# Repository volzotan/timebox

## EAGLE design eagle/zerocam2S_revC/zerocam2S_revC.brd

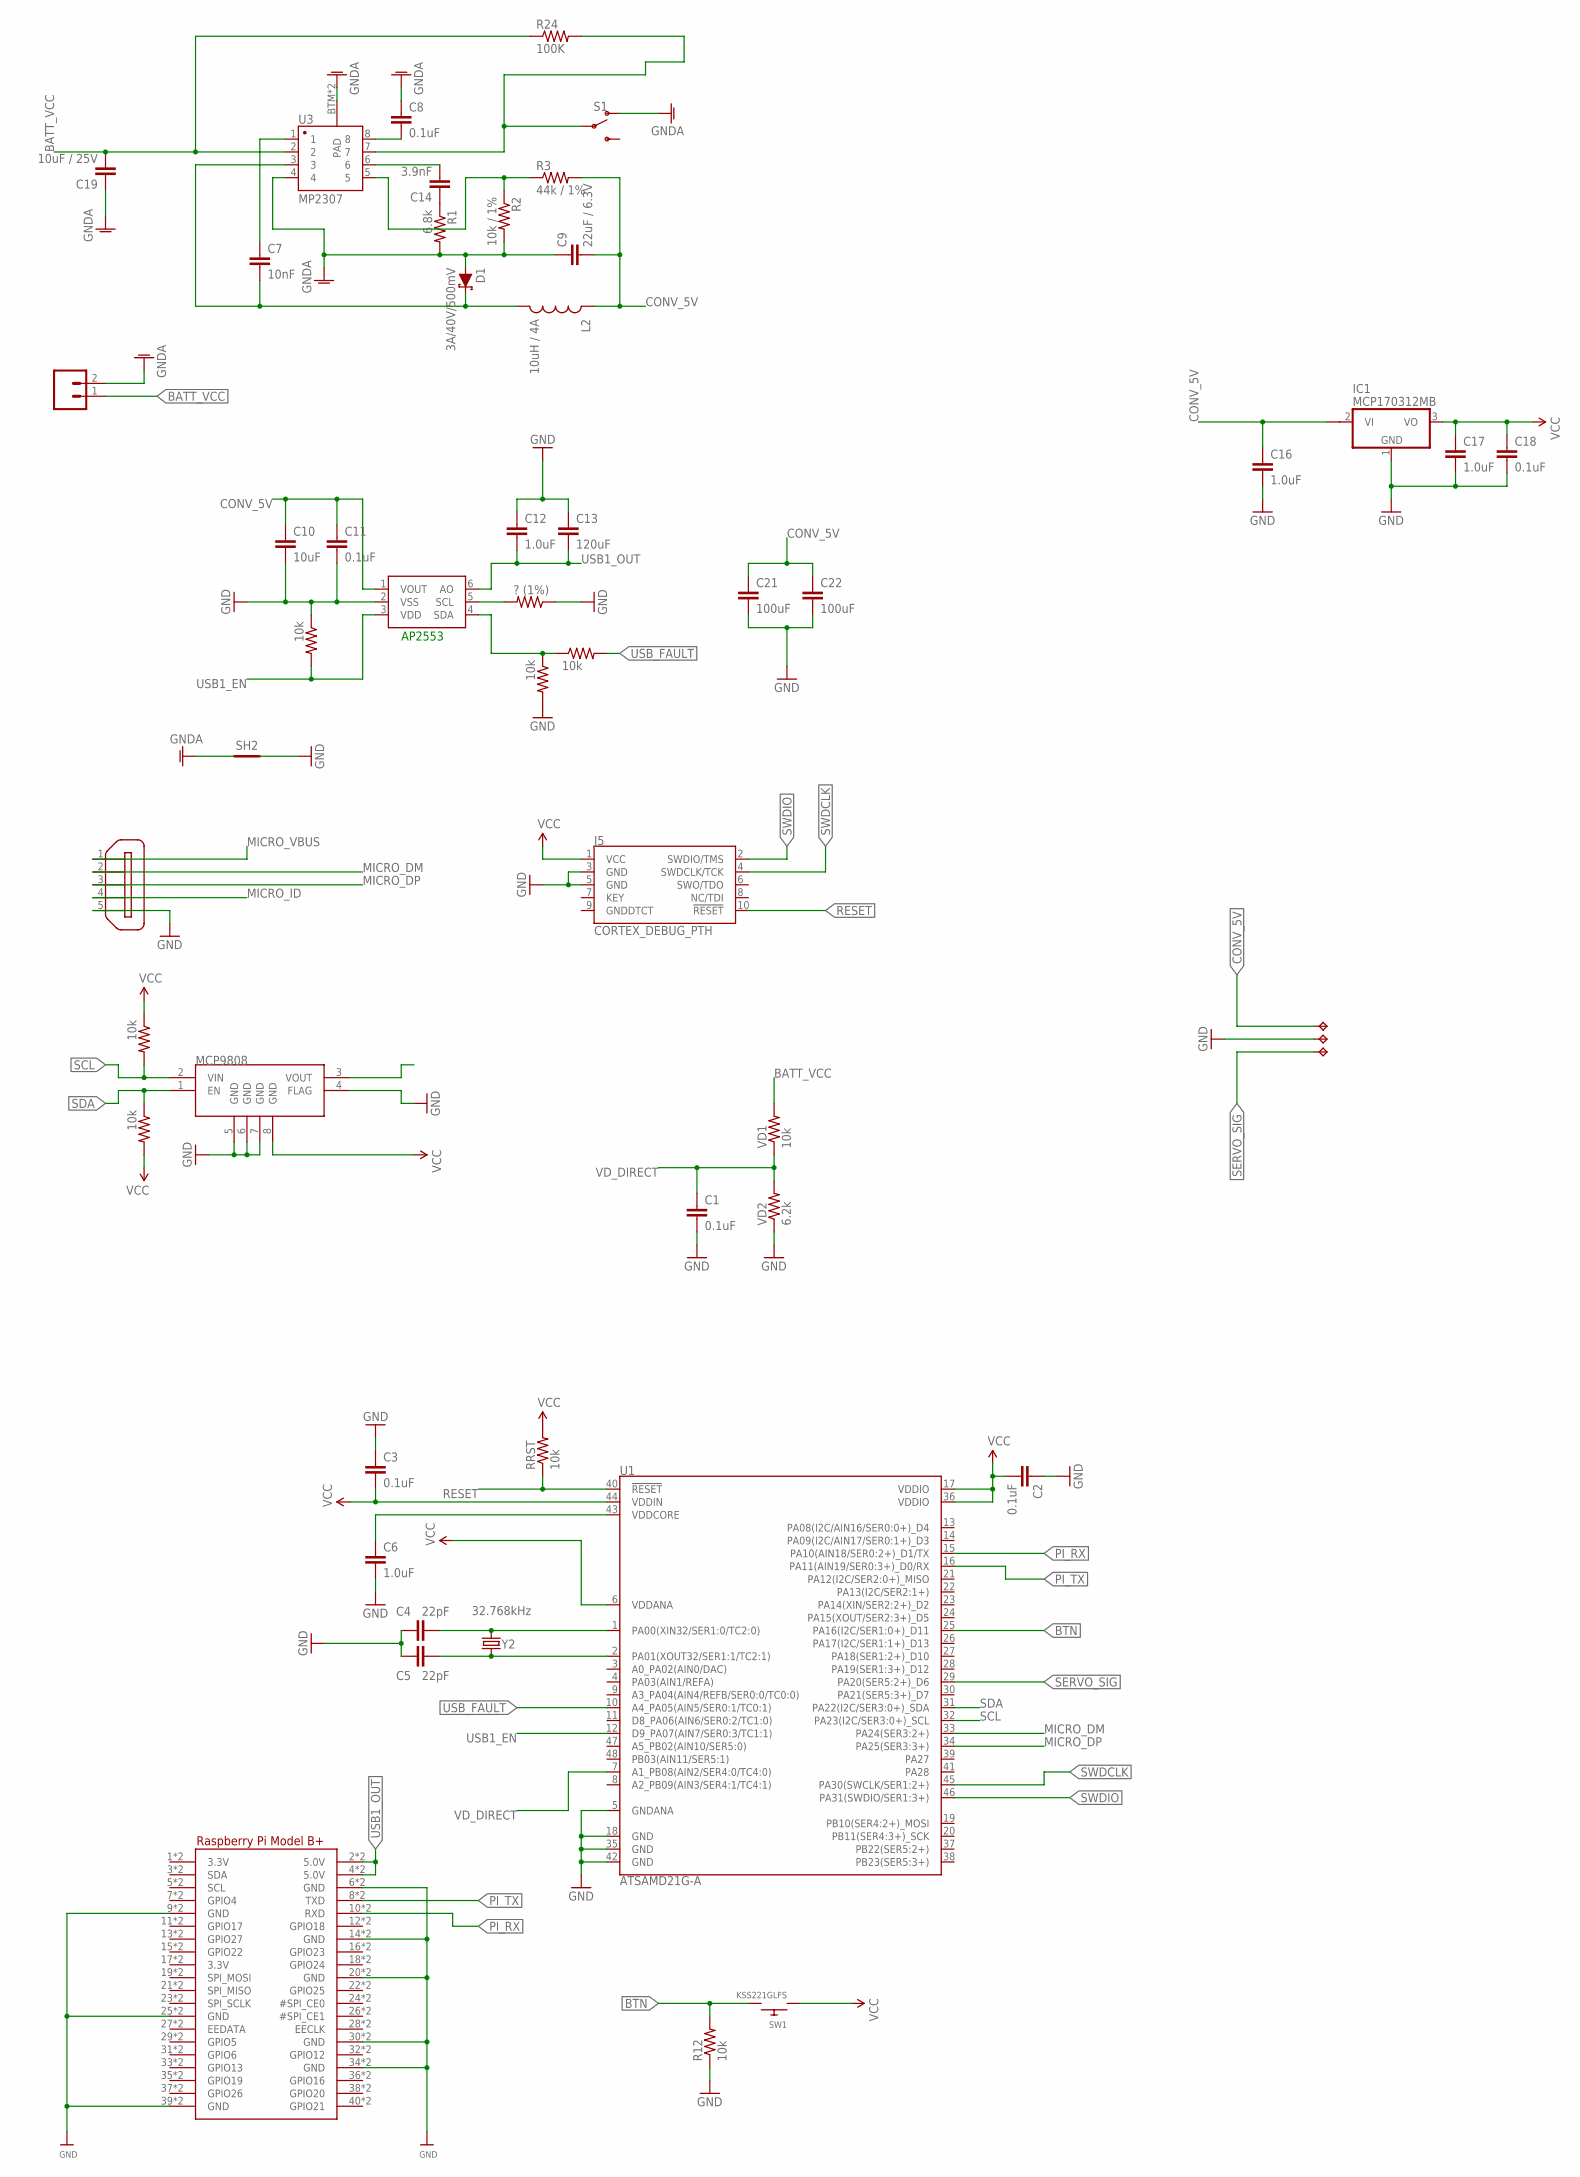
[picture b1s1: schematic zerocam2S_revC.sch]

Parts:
AP2553: MCP4725; SOT23-6
C1, C2, C3, C11, C18: 0.1uF; 0805
C4, C5: 22pF; 0805
C6, C16: 1.0uF; 0805
C7: 10nF; 0805
C8: 0.1uF; 1206
C9: 22uF / 6.3V; 1210
C10: 10uF; 0805
C12, C17: 1.0uF; 1206
C13: 120uF; 1206
C14: 3.9nF; 1206
C19: 10uF / 25V; 1210
C21, C22: 100uF; 1210
D1: 3A/40V/500mV; SMA-DIODE
IC1: MCP170312MB; SOT89
J1: CONN_023.5MM-NO_SILK; SCREWTERMINAL-3.5MM-2-NS
J5: CORTEX_DEBUG_PTH; 2X5-PTH-1.27MM
L2: 10uH / 4A; SRU1038
MCP9808: V_REG_MIC5216; MSOP8
R1: 6.8k; 1206
R2: 10k / 1%; 1206
R3: 44k / 1%; 1206
R12: 10k; 0805
R24: 100K; 1206
RPI1: RASPBERRYPI_BPLUS_BONNET_THMSMT; PI_BONNET_THMSMT
RRST: 10k; 0805
R_I2C_1, R_I2C_2: 10k; 0805
R_MOSFET_USB1: ? (1%); 0805
R_MOSFET_USB2, R_MOSFET_USB3, R_MOSFET_USB4: 10k; 0805
S1: SWITCH-SPDT-SMD-RIGHT-ANGLE; SWITCH_SPST_SMD_A
SH2: SHORT-HT5; SHORT_TOP-50
SW1: KSS221GLFS; BTN_CK_KSS
TP1, TP2, TP3: TPTP20SQ; TP20SQ
U1: ATSAMD21G-A; TQFP-48
U3: MP2307; SO08
VD1: 10k; 0805
VD2: 6.2k; 0805
X2: ZX62D-B-5PA8
Y2: 32.768kHz; CRYSTAL-SMD-3.2X1.5MM

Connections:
BATT_VCC: C19.2, J1.1, R24.1, U3.2, VD1.2
BTN: R12.2, SW1.P$2, U1.25 (PA16(I2C/SER1:0+)_D11)
CONV_5V: AP2553.1 (VOUT), C9.2, C10.1, C11.1, C16.1, C21.1, C22.1, IC1.2@1 (VI1), L2.1, R3.2, TP1.TP
GND: AP2553.2 (VSS), C1.2, C2.1, C3.1, C4.1, C5.1, C6.2, C10.2, C11.2, C12.1, C13.1, C16.2, C17.2, C18.2, C21.2, C22.2, IC1.1 (GND), J5.3 (GND), J5.5 (GND), MCP9808.4 (FLAG), MCP9808.5 (GND), MCP9808.6 (GND), MCP9808.7 (GND), R12.1, RPI1.6 (GND), RPI1.9 (GND), RPI1.14 (GND), RPI1.20 (GND), RPI1.25 (GND), RPI1.30 (GND), RPI1.34 (GND), RPI1.39 (GND), RPI1.S6 (GND), RPI1.S9 (GND), RPI1.S14 (GND), RPI1.S20 (GND), RPI1.S25 (GND), RPI1.S30 (GND), RPI1.S34 (GND), RPI1.S39 (GND), R_MOSFET_USB1.1, R_MOSFET_USB2.2, R_MOSFET_USB3.1, SH2.2, TP2.TP, U1.5 (GNDANA), U1.18 (GND), U1.35 (GND), U1.42 (GND), VD2.1, X2.5
GNDA: C8.1, C9.1, C19.1, D1.A, J1.2, R1.2, R2.2, S1.1 (O), SH2.1, U3.4, U3.BTM (PAD), U3.P$1 (PAD)
MICRO_DM: U1.33 (PA24(SER3:2+)), X2.2
MICRO_DP: U1.34 (PA25(SER3:3+)), X2.3
MICRO_ID: X2.4
MICRO_VBUS: X2.1
unnamed: C6.1, U1.43 (VDDCORE)
unnamed: AP2553.5 (SCL), R_MOSFET_USB1.2
unnamed: AP2553.4 (SDA), R_MOSFET_USB2.1, R_MOSFET_USB4.1
unnamed: C4.2, U1.1 (PA00(XIN32/SER1:0/TC2:0)), Y2.P$2 (2)
unnamed: C8.2, U3.8
unnamed: C7.2, D1.C, L2.2, U3.3
unnamed: C7.1, U3.1
unnamed: C14.1, R1.1
unnamed: C14.2, U3.6
unnamed: R2.1, R3.1, U3.5
unnamed: C5.2, U1.2 (PA01(XOUT32/SER1:1/TC2:1)), Y2.P$1 (1)
PB_BUCK_EN: R24.2, S1.2, U3.7
PI_RX: RPI1.10 (RXD), RPI1.S10 (RXD), U1.15 (PA10(AIN18/SER0:2+)_D1/TX)
PI_TX: RPI1.8 (TXD), RPI1.S8 (TXD), U1.16 (PA11(AIN19/SER0:3+)_D0/RX)
RESET: J5.10 (!RESET), RRST.1, U1.40 (!RESET!)
SCL: MCP9808.2 (VIN), R_I2C_1.2, U1.32 (PA23(I2C/SER3:0+)_SCL)
SDA: MCP9808.1 (EN), R_I2C_2.1, U1.31 (PA22(I2C/SER3:0+)_SDA)
SERVO_SIG: TP3.TP, U1.29 (PA20(SER5:2+)_D6)
SWDCLK: J5.4 (SWDCLK/TCK), U1.45 (PA30(SWCLK/SER1:2+))
SWDIO: J5.2 (SWDIO/TMS), U1.46 (PA31(SWDIO/SER1:3+))
USB1_EN: AP2553.3 (VDD), R_MOSFET_USB3.2, U1.12 (D9_PA07(AIN7/SER0:3/TC1:1))
USB1_OUT: AP2553.6 (AO), C12.2, C13.2, RPI1.2 (5.0V), RPI1.4 (5.0V), RPI1.S2 (5.0V), RPI1.S4 (5.0V)
USB_FAULT: R_MOSFET_USB4.2, U1.10 (A4_PA05(AIN5/SER0:1/TC0:1))
VCC: C2.2, C3.2, C17.1, C18.1, IC1.3 (VO), J5.1 (VCC), MCP9808.8 (GND), RRST.2, R_I2C_1.1, R_I2C_2.2, SW1.P$1, U1.6 (VDDANA), U1.17 (VDDIO), U1.36 (VDDIO), U1.44 (VDDIN)
VD_DIRECT: C1.1, U1.7 (A1_PB08(AIN2/SER4:0/TC4:0)), VD1.1, VD2.2

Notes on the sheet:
AP2553

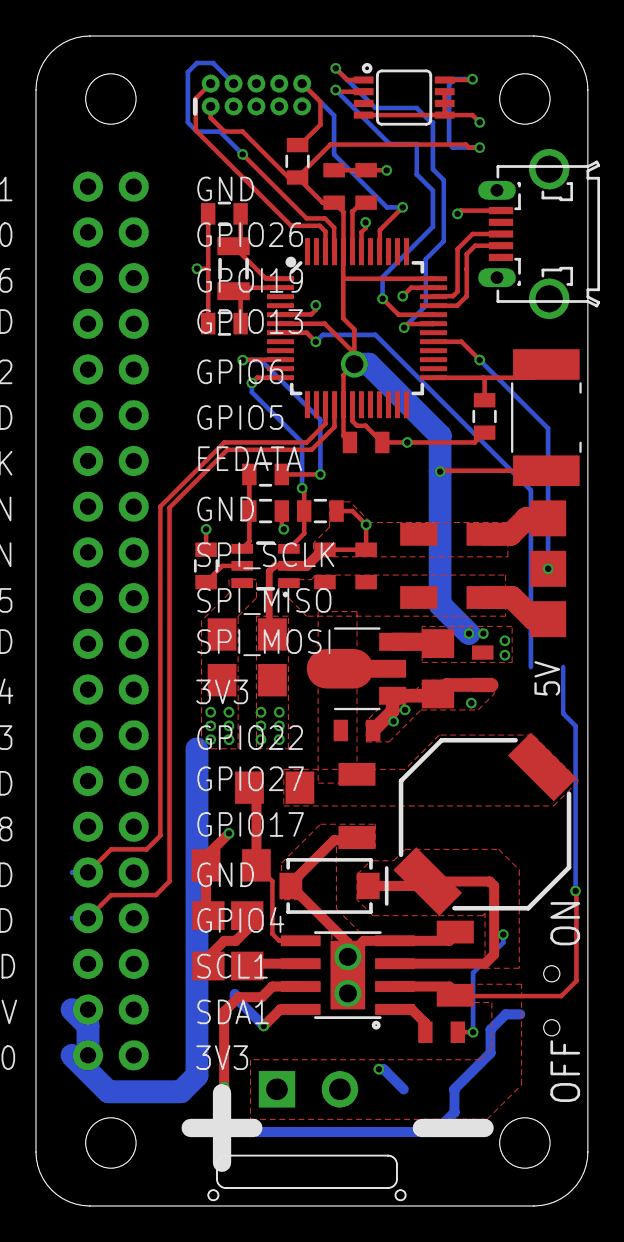
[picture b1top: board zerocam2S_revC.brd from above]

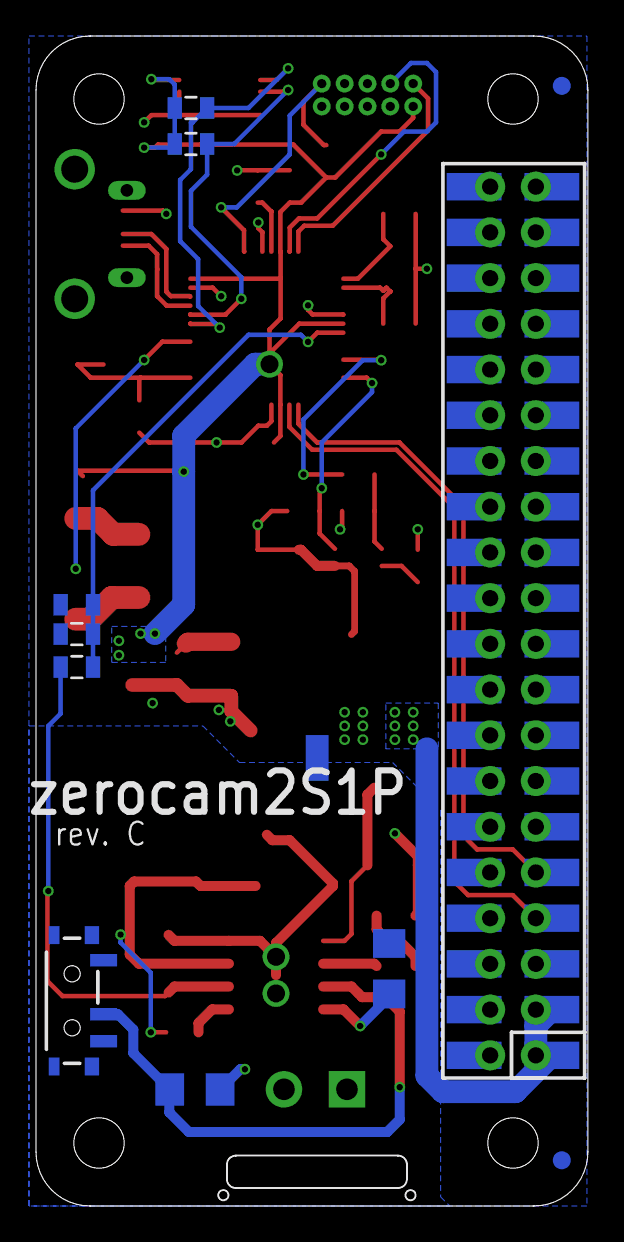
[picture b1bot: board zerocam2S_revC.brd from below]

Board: 2 copper layers, 30.7 x 65.0 mm, 52 parts (9 on the bottom side), 32 nets.

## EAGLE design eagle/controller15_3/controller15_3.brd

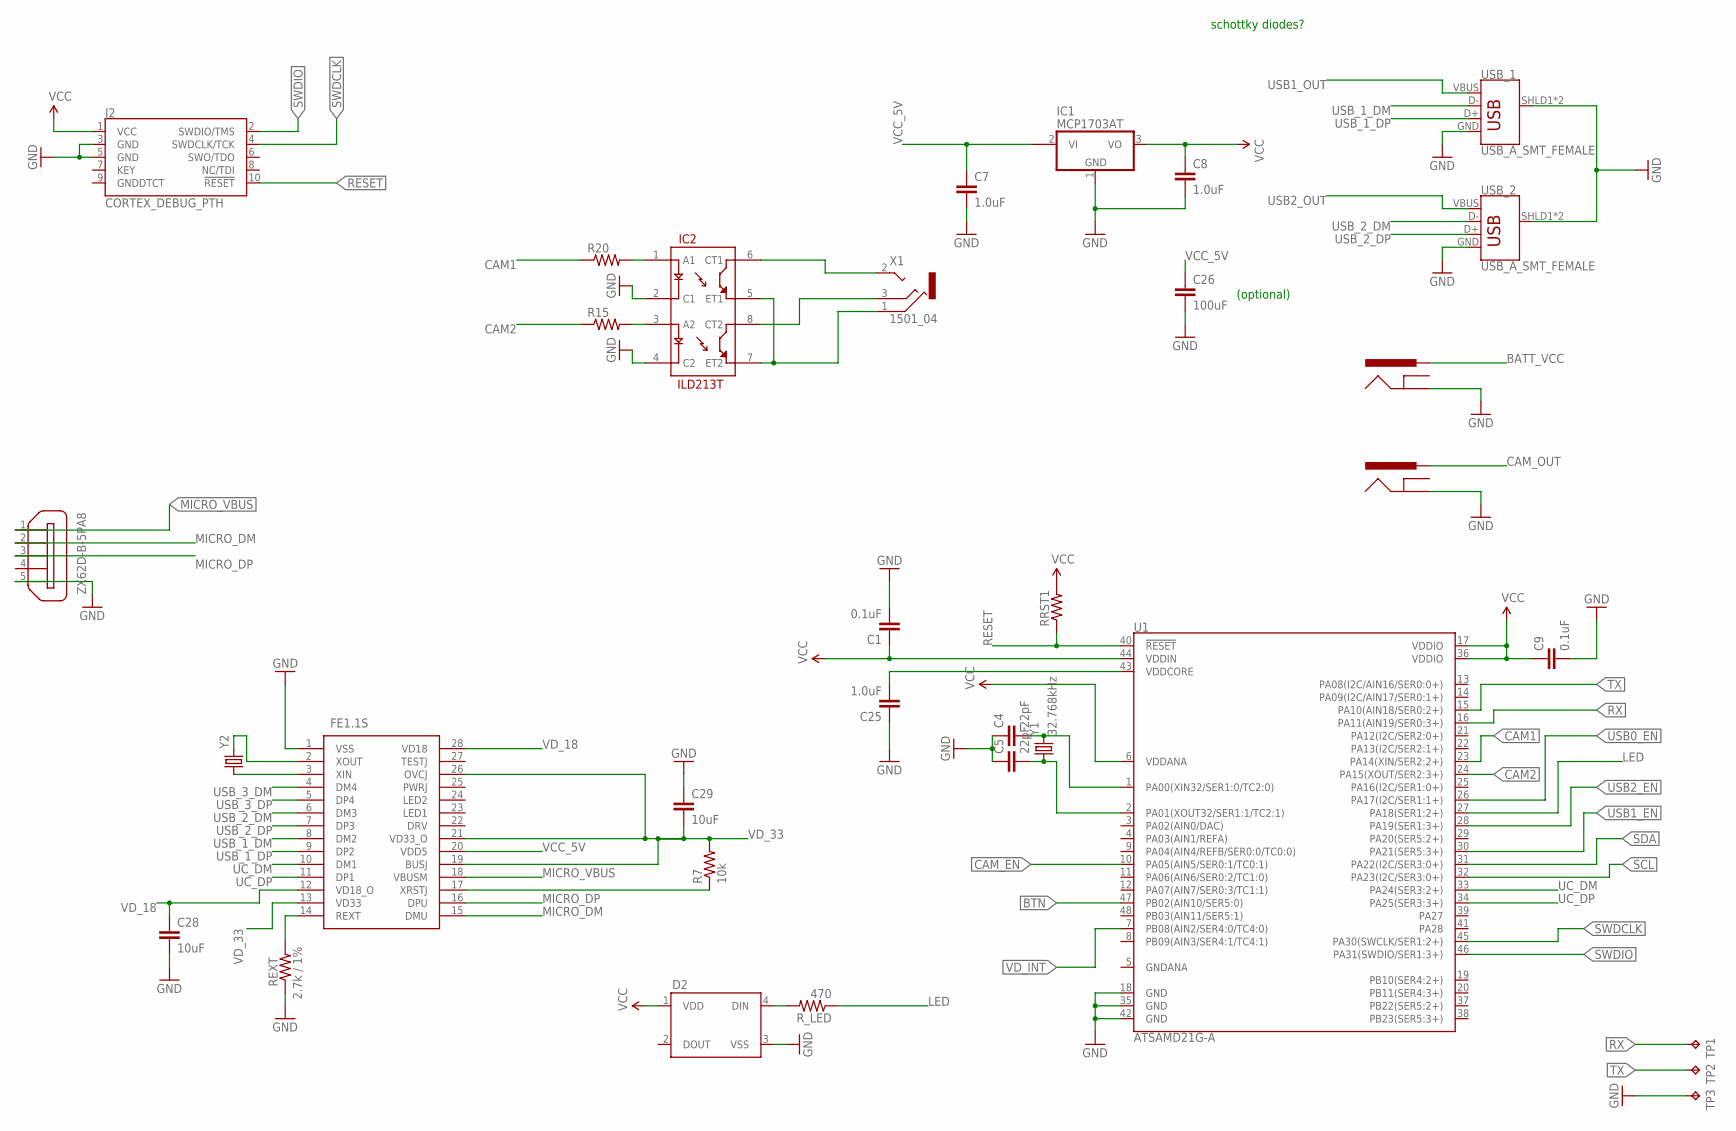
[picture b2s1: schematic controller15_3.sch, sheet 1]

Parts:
C1, C9: 0.1uF; 0805
C4, C5: 22pF; 0805
C7, C8: 1.0uF; 1206
C25: 1.0uF; 0805
C26: 100uF; 1206
C28, C29: 10uF; 0805
D2: WS2812B
IC1: MCP1703AT; SOT89
IC2: ILD213T; SO08
IC3: FE1.1S; SOP64P600X175-28N
J2: CORTEX_DEBUG_PTH; 2X5-PTH-1.27MM
J3, J4: POWER_JACKPTH_BREAD; POWER_JACK_PTH_BREAD
R7: 10k; 0805
R15, R20: RESISTOR0805-RES; 0805
REXT: 2.7k / 1%; 0805
RRST1: RESISTOR0805-RES; 0805
R_LED: 470; 0805
TP1, TP2, TP3: TPB2,54; B2,54
U1: ATSAMD21G-A; TQFP-48
USB_1, USB_2: USB_A_SMT_FEMALE; USB-A-S-SILK-FEMALE
X1: 1501_04; 1501_05
X2: ZX62D-B-5PA8
Y1: 32.768kHz; CRYSTAL-SMD-3.2X1.5MM
Y2: 12MHz; CRYSTAL-SMD-5X3

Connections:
BATT_VCC: J4.PWR; also elsewhere on the board
BTN: U1.47 (PB02(AIN10/SER5:0))
CAM1: R20.1, U1.23 (PA14(XIN/SER2:2+))
CAM2: R15.1, U1.24 (PA15(XOUT/SER2:3+))
CAM_EN: U1.10 (PA05(AIN5/SER0:1/TC0:1)); also elsewhere on the board
CAM_OUT: J3.PWR; also elsewhere on the board
GND: C1.2, C4.1, C5.1, C7.2, C8.2, C9.2, C25.1, C26.2, C28.2, C29.1, D2.3 (VSS), IC1.1 (GND), IC2.2 (C1), IC2.4 (C2), IC3.1 (VSS), J2.3 (GND), J2.5 (GND), J3.GND, J4.GND, REXT.1, TP3.TP, U1.18 (GND), U1.35 (GND), U1.42 (GND), USB_1.GND, USB_1.SHLD1 (SHIELD), USB_1.SHLD2 (SHIELD), USB_2.GND, USB_2.SHLD1 (SHIELD), USB_2.SHLD2 (SHIELD), X2.5; also elsewhere on the board
LED: R_LED.1, U1.27 (PA18(SER1:2+))
MICRO_DM: IC3.15 (DMU), X2.2
MICRO_DP: IC3.16 (DPU), X2.3
MICRO_VBUS: IC3.18 (VBUSM), X2.1; also elsewhere on the board
unnamed: IC2.3 (A2), R15.2
unnamed: C25.2, U1.43 (VDDCORE)
unnamed: D2.4 (DIN), R_LED.2
unnamed: C4.2, U1.1 (PA00(XIN32/SER1:0/TC2:0)), Y1.P$2 (2)
unnamed: IC2.6 (CT1), X1.2
unnamed: IC2.8 (CT2), X1.3
unnamed: IC3.17 (XRSTJ), R7.1
unnamed: IC2.1 (A1), R20.2
unnamed: IC3.3 (XIN), Y2.1
unnamed: IC3.2 (XOUT), Y2.3 (2)
unnamed: IC3.14 (REXT), REXT.2
unnamed: C5.2, U1.2 (PA01(XOUT32/SER1:1/TC2:1)), Y1.P$1 (1)
unnamed: IC2.5 (ET1), IC2.7 (ET2), X1.1
RESET: J2.10 (!RESET), RRST1.1, U1.40 (!RESET!)
RX: TP1.TP, U1.16 (PA11(AIN19/SER0:3+))
SCL: U1.32 (PA23(I2C/SER3:0+)); also elsewhere on the board
SDA: U1.31 (PA22(I2C/SER3:0+)); also elsewhere on the board
SWDCLK: J2.4 (SWDCLK/TCK), U1.45 (PA30(SWCLK/SER1:2+))
SWDIO: J2.2 (SWDIO/TMS), U1.46 (PA31(SWDIO/SER1:3+))
TX: TP2.TP, U1.15 (PA10(AIN18/SER0:2+))
UC_DM: IC3.10 (DM1), U1.33 (PA24(SER3:2+))
UC_DP: IC3.11 (DP1), U1.34 (PA25(SER3:3+))
USB0_EN: U1.26 (PA17(I2C/SER1:1+)); also elsewhere on the board
USB1_EN: U1.30 (PA21(SER5:3+)); also elsewhere on the board
USB1_OUT: USB_1.VBUS; also elsewhere on the board
USB2_EN: U1.28 (PA19(SER1:3+)); also elsewhere on the board
USB2_OUT: USB_2.VBUS; also elsewhere on the board
USB_1_DM: IC3.8 (DM2), USB_1.D-
USB_1_DP: IC3.9 (DP2), USB_1.D+
USB_2_DM: IC3.6 (DM3), USB_2.D-
USB_2_DP: IC3.7 (DP3), USB_2.D+
USB_3_DM: IC3.4 (DM4)
USB_3_DP: IC3.5 (DP4)
VCC: C1.1, C8.1, C9.1, D2.1 (VDD), IC1.3 (VO), J2.1 (VCC), RRST1.2, U1.6 (VDDANA), U1.17 (VDDIO), U1.36 (VDDIO), U1.44 (VDDIN); also elsewhere on the board
VCC_5V: C7.1, C26.1, IC1.2@1 (VI1), IC3.20 (VDD5); also elsewhere on the board
VD_18: C28.1, IC3.12 (VD18_O), IC3.28 (VD18)
VD_33: C29.2, IC3.13 (VD33), IC3.19 (BUSJ), IC3.21 (VD33_O), IC3.26 (OVCJ), R7.2
VD_INT: U1.7 (PB08(AIN2/SER4:0/TC4:0)); also elsewhere on the board

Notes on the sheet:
schottky diodes?
(optional)

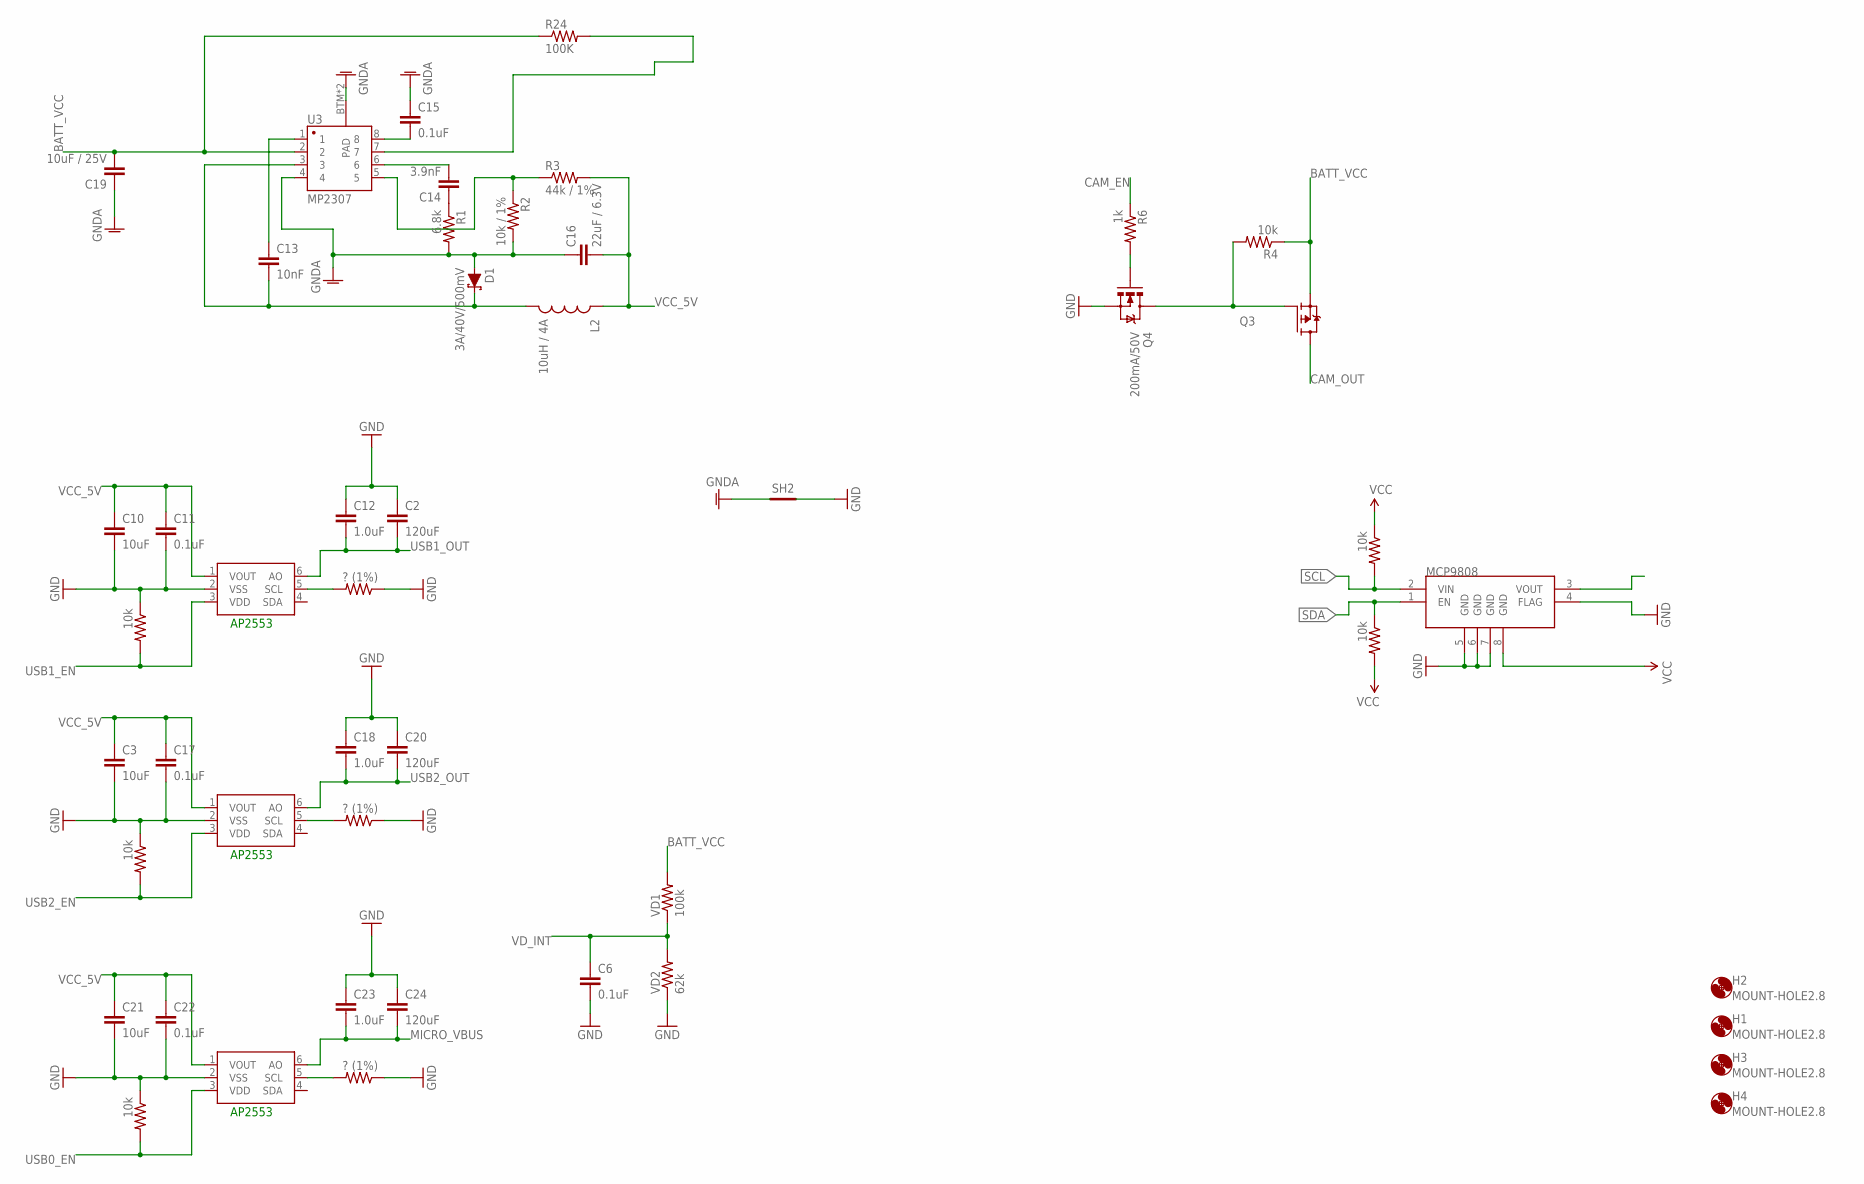
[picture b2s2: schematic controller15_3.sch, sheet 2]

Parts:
AP1, AP2, AP2553: MCP4725; SOT23-6
C2, C20, C24: 120uF; 1206
C3, C10, C21: 10uF; 1206
C6, C15: 0.1uF; 1206
C11, C17, C22: 0.1uF; 0805
C12, C18, C23: 1.0uF; 1206
C13: 10nF; 1206
C14: 3.9nF; 1206
C16: 22uF / 6.3V; 1210
C19: 10uF / 25V; 1210
D1: 3A/40V/500mV; SMA-DIODE
H1, H2, H3, H4: MOUNT-HOLE2.8; 2,8
L2: 10uH / 4A; SRU1038
MCP9808: V_REG_MIC5216; MSOP8
Q3: FDD4141TO252; TO252
Q4: 200mA/50V; SOT23-3
R1: 6.8k; 1206
R2: 10k / 1%; 1206
R3: 44k / 1%; 1206
R4: 10k; 0805
R6: 1k; 0805
R24: 100K; 1206
R_I2C_1, R_I2C_2: 10k; 0805
R_MOSFET_USB1, R_MOSFET_USB2, R_MOSFET_USB5: ? (1%); 0805
R_MOSFET_USB3, R_MOSFET_USB4, R_MOSFET_USB6: 10k; 0805
SH2: SHORT-HT5; SHORT_TOP-50
U3: MP2307; SO08
VD1: 100k; 1206
VD2: 62k; 1206

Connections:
BATT_VCC: C19.2, Q3.2 (S), R4.1, R24.1, U3.2, VD1.2; also elsewhere on the board
CAM_EN: R6.1; also elsewhere on the board
CAM_OUT: Q3.3 (D); also elsewhere on the board
GND: AP1.2 (VSS), AP2.2 (VSS), AP2553.2 (VSS), C2.1, C3.2, C6.2, C10.2, C11.2, C12.1, C17.2, C18.1, C20.1, C21.2, C22.2, C23.1, C24.1, MCP9808.4 (FLAG), MCP9808.5 (GND), MCP9808.6 (GND), MCP9808.7 (GND), Q4.2 (S), R_MOSFET_USB1.1, R_MOSFET_USB2.1, R_MOSFET_USB3.1, R_MOSFET_USB4.1, R_MOSFET_USB5.1, R_MOSFET_USB6.1, SH2.2, VD2.1; also elsewhere on the board
GNDA: C15.1, C16.1, C19.1, D1.A, R1.2, R2.2, SH2.1, U3.4, U3.BTM (PAD), U3.P$1 (PAD)
MICRO_VBUS: AP2.6 (AO), C23.2, C24.2; also elsewhere on the board
unnamed: Q4.1 (G), R6.2
unnamed: Q3.1 (G), Q4.3 (D), R4.2
unnamed: AP2553.5 (SCL), R_MOSFET_USB1.2
unnamed: AP1.5 (SCL), R_MOSFET_USB2.2
unnamed: AP2.5 (SCL), R_MOSFET_USB5.2
unnamed: C15.2, U3.8
unnamed: C13.2, D1.C, L2.2, U3.3
unnamed: C13.1, U3.1
unnamed: C14.1, R1.1
unnamed: C14.2, U3.6
unnamed: R2.1, R3.1, U3.5
PB_BUCK_EN: R24.2, U3.7
SCL: MCP9808.2 (VIN), R_I2C_1.2; also elsewhere on the board
SDA: MCP9808.1 (EN), R_I2C_2.1; also elsewhere on the board
USB0_EN: AP2.3 (VDD), R_MOSFET_USB6.2; also elsewhere on the board
USB1_EN: AP2553.3 (VDD), R_MOSFET_USB3.2; also elsewhere on the board
USB1_OUT: AP2553.6 (AO), C2.2, C12.2; also elsewhere on the board
USB2_EN: AP1.3 (VDD), R_MOSFET_USB4.2; also elsewhere on the board
USB2_OUT: AP1.6 (AO), C18.2, C20.2; also elsewhere on the board
VCC: MCP9808.8 (GND), R_I2C_1.1, R_I2C_2.2; also elsewhere on the board
VCC_5V: AP1.1 (VOUT), AP2.1 (VOUT), AP2553.1 (VOUT), C3.1, C10.1, C11.1, C16.2, C17.1, C21.1, C22.1, L2.1, R3.2; also elsewhere on the board
VD_INT: C6.1, VD1.1, VD2.2; also elsewhere on the board

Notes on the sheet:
AP2553

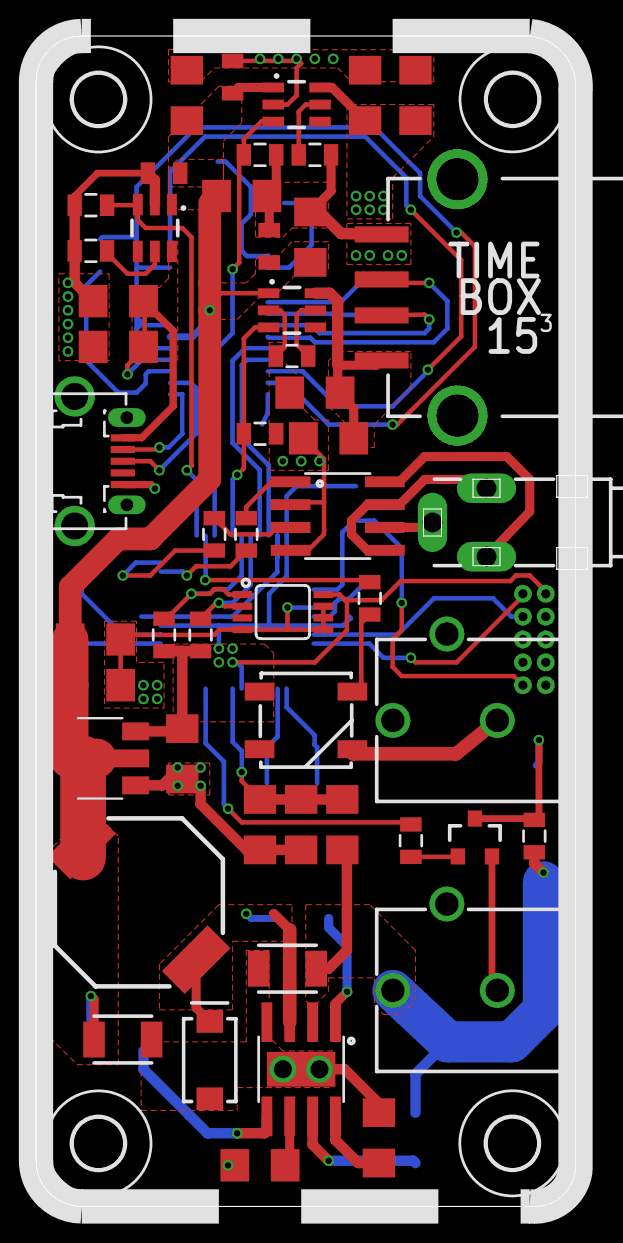
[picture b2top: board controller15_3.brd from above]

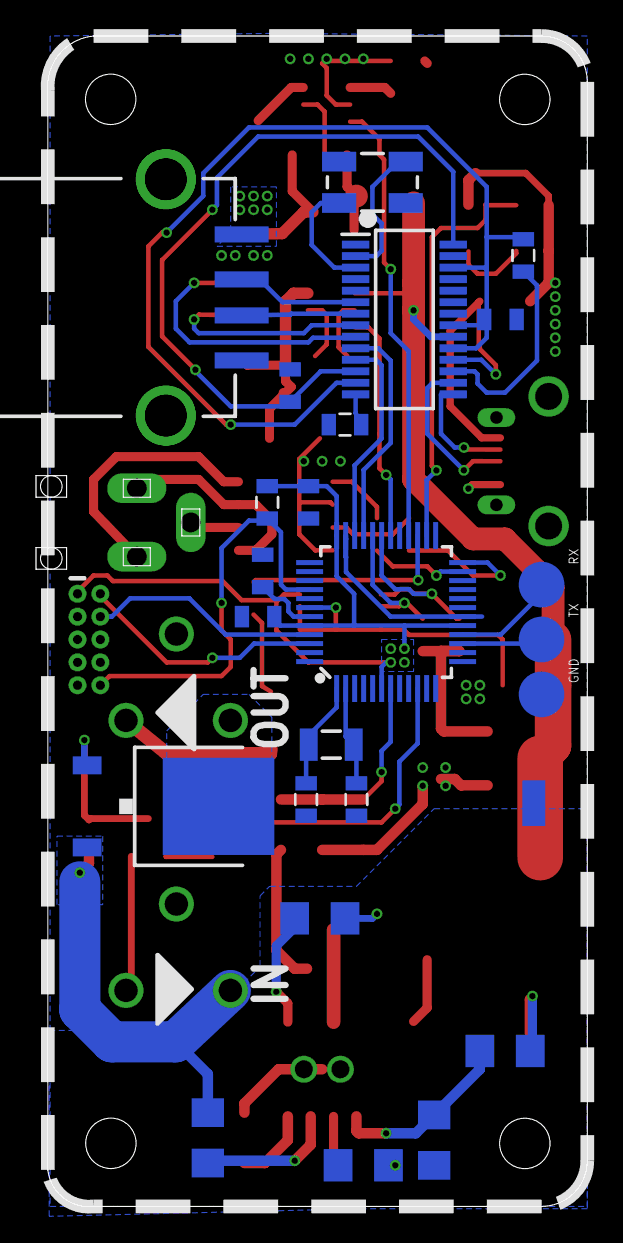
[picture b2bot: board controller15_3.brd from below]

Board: 2 copper layers, 30.6 x 65.0 mm, 81 parts (26 on the bottom side), 59 nets.

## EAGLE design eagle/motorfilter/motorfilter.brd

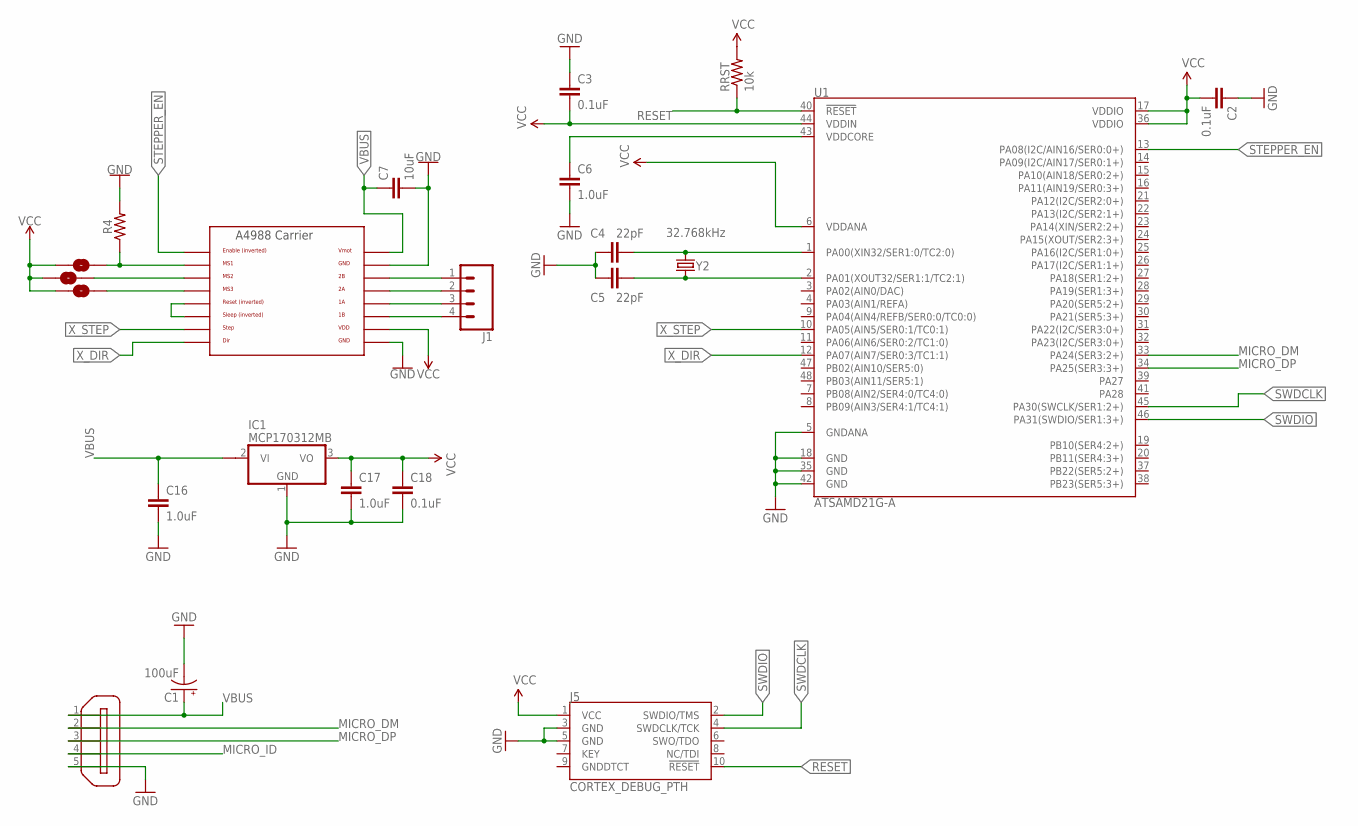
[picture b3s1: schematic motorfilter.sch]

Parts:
C1: 100uF; PANASONIC_D
C2, C3, C18: 0.1uF; 0805
C4, C5: 22pF; 0805
C6, C16: 1.0uF; 0805
C7: 10uF; 1206
C17: 1.0uF; 1206
IC1: MCP170312MB; SOT89
J1: CONN_04SCREW; SCREWTERMINAL-3.5MM-4
J5: CORTEX_DEBUG_PTH; 2X5-PTH-1.27MM
JP4, JP5, JP6: JUMPER-SMT_2_NO_SILK_ROUND; SMT-JUMPER_2_NO_SILK_ROUND
R4: 0805
RRST: 10k; 0805
U1: ATSAMD21G-A; TQFP-48
U$2: A4988BREAKOUT
X2: ZX62D-B-5PA8
Y2: 32.768kHz; CRYSTAL-SMD-3.2X1.5MM

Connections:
GND: C1.-, C2.1, C3.1, C4.1, C5.1, C6.2, C7.2, C16.2, C17.2, C18.2, IC1.1 (GND), J5.3 (GND), J5.5 (GND), R4.2, U1.5 (GNDANA), U1.18 (GND), U1.35 (GND), U1.42 (GND), U$2.GND, U$2.GND@0 (GND), X2.5
MICRO_DM: U1.33 (PA24(SER3:2+)), X2.2
MICRO_DP: U1.34 (PA25(SER3:3+)), X2.3
MICRO_ID: X2.4
unnamed: C6.1, U1.43 (VDDCORE)
unnamed: J1.1, U$2.2B
unnamed: J1.2, U$2.2A
unnamed: J1.3, U$2.1A
unnamed: J1.4, U$2.1B
unnamed: C4.2, U1.1 (PA00(XIN32/SER1:0/TC2:0)), Y2.P$2 (2)
unnamed: JP6.2, U$2.MS3
unnamed: U$2.RST, U$2.SLP (SLEEP)
unnamed: JP4.2, R4.1, U$2.MS1
unnamed: JP5.2, U$2.MS2
unnamed: C5.2, U1.2 (PA01(XOUT32/SER1:1/TC2:1)), Y2.P$1 (1)
RESET: J5.10 (!RESET), RRST.1, U1.40 (!RESET!)
STEPPER_EN: U1.13 (PA08(I2C/AIN16/SER0:0+)), U$2.EN
SWDCLK: J5.4 (SWDCLK/TCK), U1.45 (PA30(SWCLK/SER1:2+))
SWDIO: J5.2 (SWDIO/TMS), U1.46 (PA31(SWDIO/SER1:3+))
VBUS: C1.+, C7.1, C16.1, IC1.2@1 (VI1), U$2.VMOT, X2.1
VCC: C2.2, C3.2, C17.1, C18.1, IC1.3 (VO), J5.1 (VCC), JP4.1, JP5.1, JP6.1, RRST.2, U1.6 (VDDANA), U1.17 (VDDIO), U1.36 (VDDIO), U1.44 (VDDIN), U$2.VDD
X_DIR: U1.12 (PA07(AIN7/SER0:3/TC1:1)), U$2.DIR
X_STEP: U1.10 (PA05(AIN5/SER0:1/TC0:1)), U$2.STEP

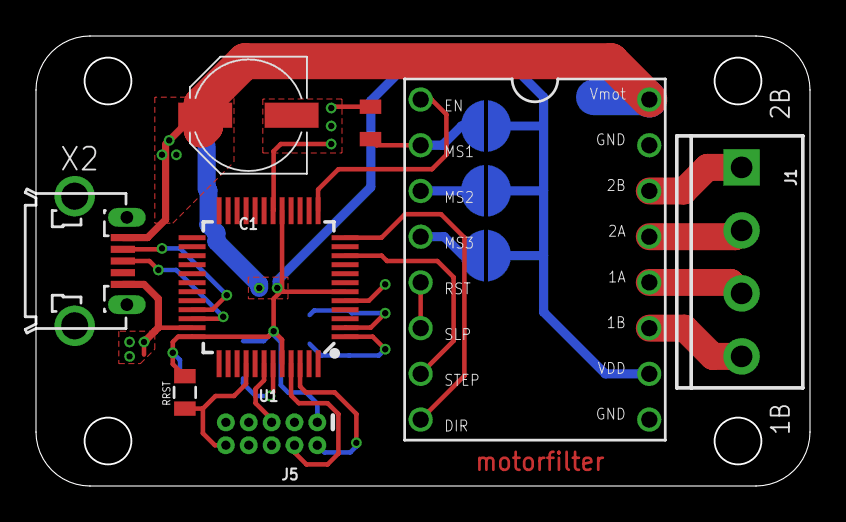
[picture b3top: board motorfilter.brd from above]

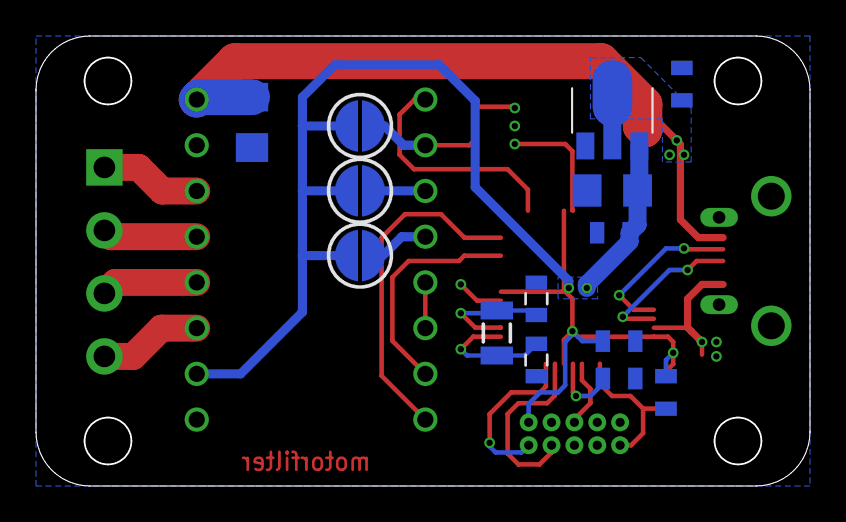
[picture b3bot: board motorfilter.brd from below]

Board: 2 copper layers, 43.0 x 25.0 mm, 22 parts (14 on the bottom side), 22 nets.

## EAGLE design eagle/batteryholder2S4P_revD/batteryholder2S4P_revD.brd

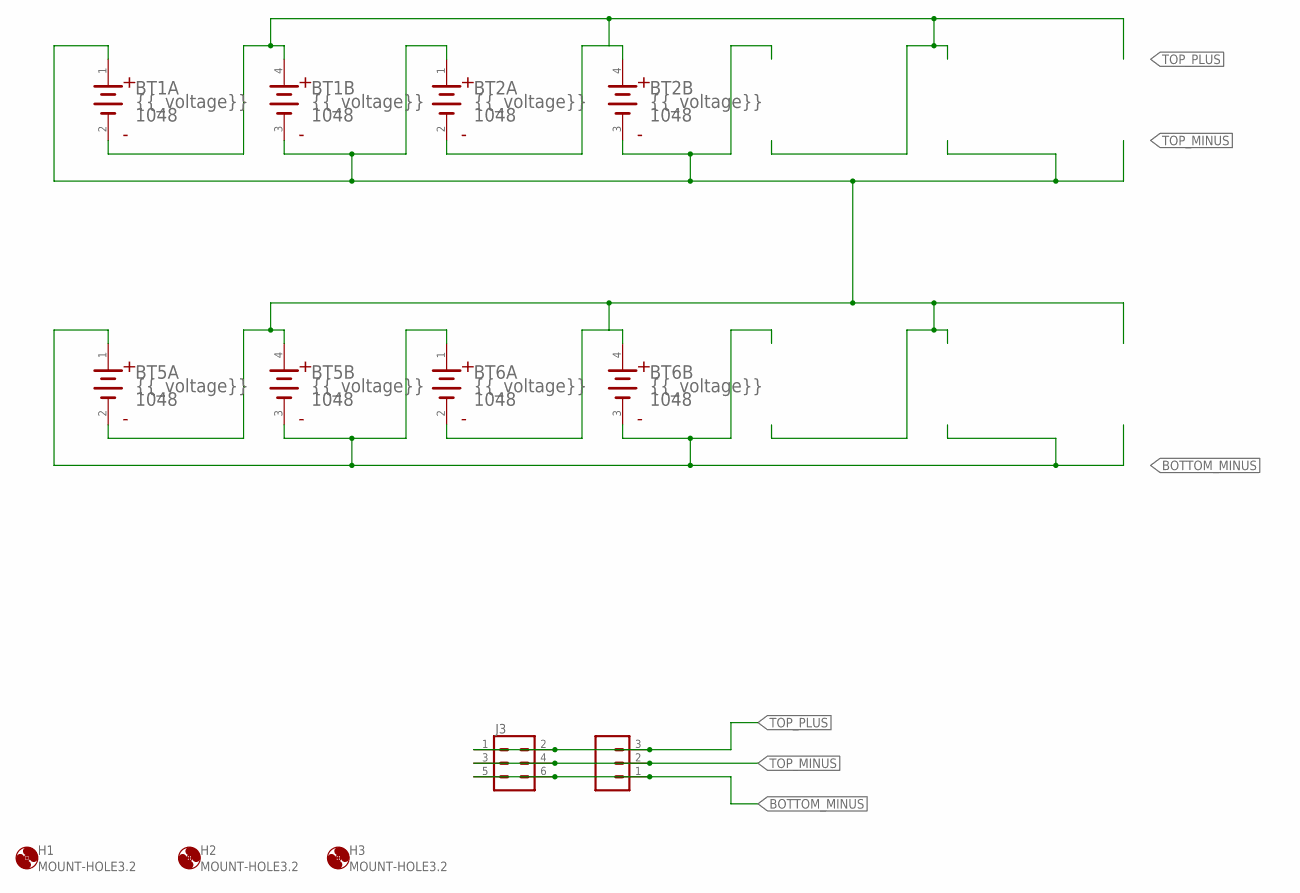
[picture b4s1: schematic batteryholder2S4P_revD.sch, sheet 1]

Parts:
BT1, BT2, BT5, BT6: KEYSTONE_1048KEYSTONE_1048_0_0; KEYSTONE_1048_0
H1, H2, H3: MOUNT-HOLE3.2; 3,2
J1: CONN_03-SCREW-5MM; SCREWTERMINAL-5MM-3
J3: CONN_03X2SHROUD; 2X3-SHROUDED

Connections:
BOTTOM_MINUS: BT5.1 (1_ANODE), BT5.3 (2_CATHODE), BT6.1 (1_ANODE), BT6.3 (2_CATHODE), J1.1, J3.5, J3.6; also elsewhere on the board
TOP_MINUS: BT1.1 (1_ANODE), BT1.3 (2_CATHODE), BT2.1 (1_ANODE), BT2.3 (2_CATHODE), BT5.2 (1_CATHODE), BT5.4 (2_ANODE), BT6.2 (1_CATHODE), BT6.4 (2_ANODE), J1.2, J3.3, J3.4; also elsewhere on the board
TOP_PLUS: BT1.2 (1_CATHODE), BT1.4 (2_ANODE), BT2.2 (1_CATHODE), BT2.4 (2_ANODE), J1.3, J3.1, J3.2; also elsewhere on the board

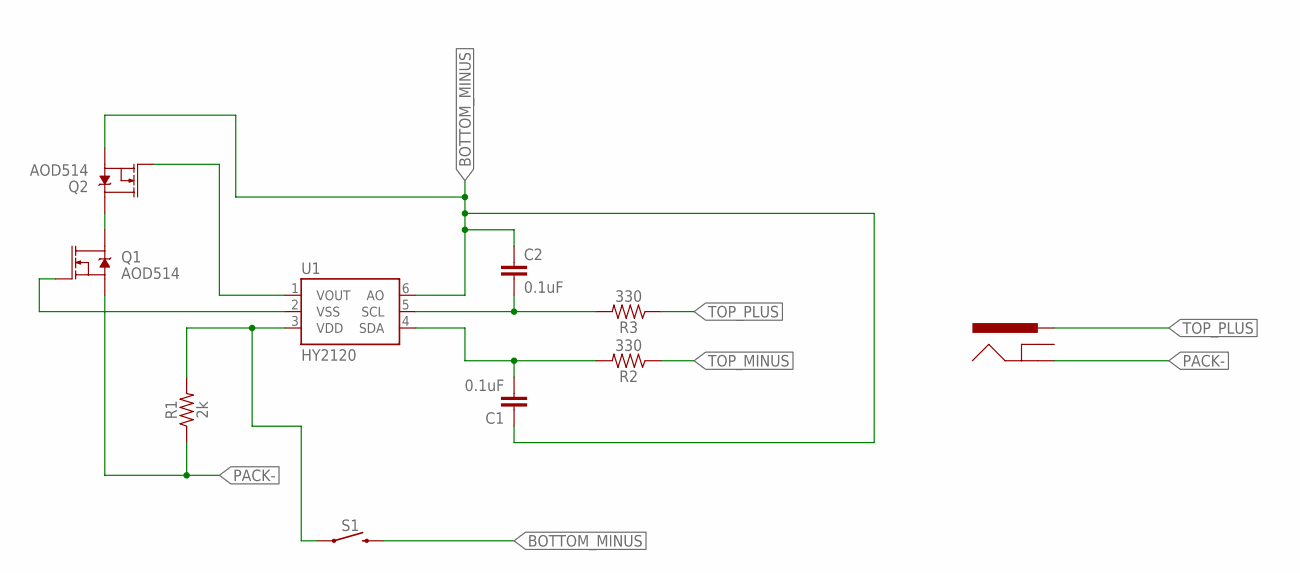
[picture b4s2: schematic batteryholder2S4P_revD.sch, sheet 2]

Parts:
C1, C2: 0.1uF; 1206
J2: POWER_JACKPTH_BREAD; POWER_JACK_PTH_BREAD
Q1, Q2: AOD514; DPAK
R1: 2k; 1206
R2, R3: 330; 1206
S1: MOMENTARY-SWITCH-SPST-PTH-6.0MM; TACTILE_SWITCH_PTH_6.0MM
U1: HY2120; SOT23-6

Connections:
BOTTOM_MINUS: C1.1, C2.1, Q2.3 (S), S1.3 (2), U1.6 (AO); also elsewhere on the board
unnamed: Q2.1 (G), U1.1 (VOUT)
unnamed: Q1.1 (G), U1.2 (VSS)
unnamed: R1.2, S1.1, U1.3 (VDD)
unnamed: C2.2, R3.2, U1.5 (SCL)
unnamed: C1.2, R2.2, U1.4 (SDA)
unnamed: Q1.4 (D), Q2.4 (D)
PACK-: J2.GND, Q1.3 (S), R1.1
TOP_MINUS: R2.1; also elsewhere on the board
TOP_PLUS: J2.PWR, R3.1; also elsewhere on the board

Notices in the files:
parts and their libraries:
SparkFun-Connectors: Licensing: Creative Commons ShareAlike 4.0 International - https://creativecommons.org/licenses/by-sa/4.0
